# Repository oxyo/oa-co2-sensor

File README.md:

## Open Automation wireless CO2 sensor    

This device has been made on NXP LPC1114FN28 ARM MCU with winsensor CO2 sensor connected.
It uses [Ciseco XRF wireless RF radio UART serial data module][] to communicate with Open Automation Center

This simple device can measure CO2 concentration in air up to 2000 ppms. 
  
MBED firmware, schematics and board files provided. 
  
For more information please visit [openautomation.center](http://openautomation.center)

Licensed under [WTFPL license terms](http://www.wtfpl.net/)

[Ciseco XRF wireless RF radio UART serial data module]: http://shop.ciseco.co.uk/xrf-wireless-rf-radio-uart-serial-data-module-xbee-shaped/

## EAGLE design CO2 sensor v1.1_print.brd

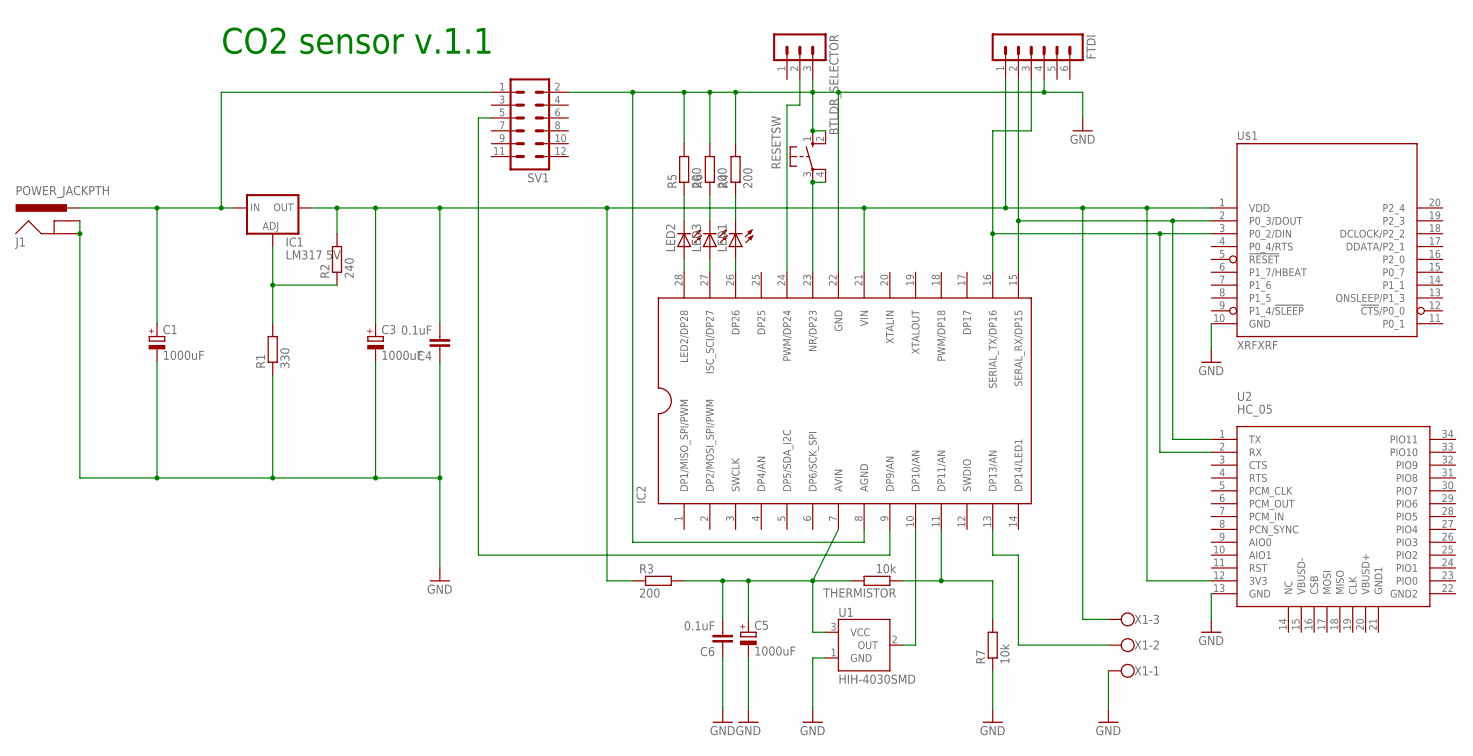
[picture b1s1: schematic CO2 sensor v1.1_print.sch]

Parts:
BTLDR_SELECTOR: MA03-1
C1, C3, C5: 1000uF; E5-10,5
C4, C6: 0.1uF; C050-025X075
FTDI: MA06-1
IC1: LM317 5V; 317TL
IC2: LPC1114FN28; DIP28
J1: POWER_JACKPTH; POWER_JACK_PTH
LED1, LED2, LED3: LED3MM
R1: 330; 0207/10
R2: 240; 0207/12
R3, R6: 200; 0207/12
R4: 200; 0207/10
R5: 200; 0207/2V
R7: 10k; 0207/12
RESETSW: 10-XX; B3F-10XX
SV1: MA06-2
THERMISTOR: 10k; 0207/5V
U1: HIH-4030SMD; HIH-4030
U2: HC_05; BLUETOOTH_SMD
U$1: XRFXRF; XRF
X1: W237-103

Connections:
GND: BTLDR_SELECTOR.3, C1.-, C3.-, C4.1, C5.-, C6.1, FTDI.4, IC2.8 (AGND), IC2.22 (GND), J1.GND, J1.GNDBREAK, R1.1, R4.2, R5.2, R6.2, R7.1, RESETSW.1 (S), RESETSW.2 (S1), SV1.2, U1.1 (GND), U2.13 (GND), U$1.10 (GND), X1.1
INPUT-CO2: IC2.9 (DP9/AN), SV1.5
INPUT-T: IC2.11 (DP11/AN), R7.2, THERMISTOR.1
INPUT-X: IC2.13 (DP13/AN), X1.2
LM317-5V: IC1.1 (ADJ), R1.2, R2.1
unnamed: LED1.K (C), R4.1
unnamed: IC2.28 (LED2/DP28), LED2.A
unnamed: C5.+, C6.2, IC2.7 (AVIN), R3.2, THERMISTOR.2, U1.3 (VCC)
unnamed: IC2.27 (ISC_SCI/DP27), LED3.A
unnamed: IC2.26 (DP26), LED1.A
unnamed: FTDI.2, IC2.15 (SERAL_RX/DP15), U2.1 (TX), U$1.2 (P0_3/DOUT)
unnamed: FTDI.3, IC2.16 (SERIAL_TX/DP16), U2.2 (RX), U$1.3 (P0_2/DIN)
unnamed: IC2.10 (DP10/AN), U1.2 (OUT)
unnamed: LED3.K (C), R6.1
unnamed: LED2.K (C), R5.1
unnamed: IC2.23 (NR/DP23), RESETSW.3, RESETSW.4 (P1)
unnamed: BTLDR_SELECTOR.2, IC2.24 (PWM/DP24)
V3.3: C3.+, C4.2, FTDI.1, IC1.2 (OUT), IC2.21 (VIN), R2.2, R3.1, U2.12 (3V3), U$1.1 (VDD), X1.3
V5: C1.+, IC1.3 (IN), J1.PWR, SV1.1

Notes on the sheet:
CO2 sensor v.1.1

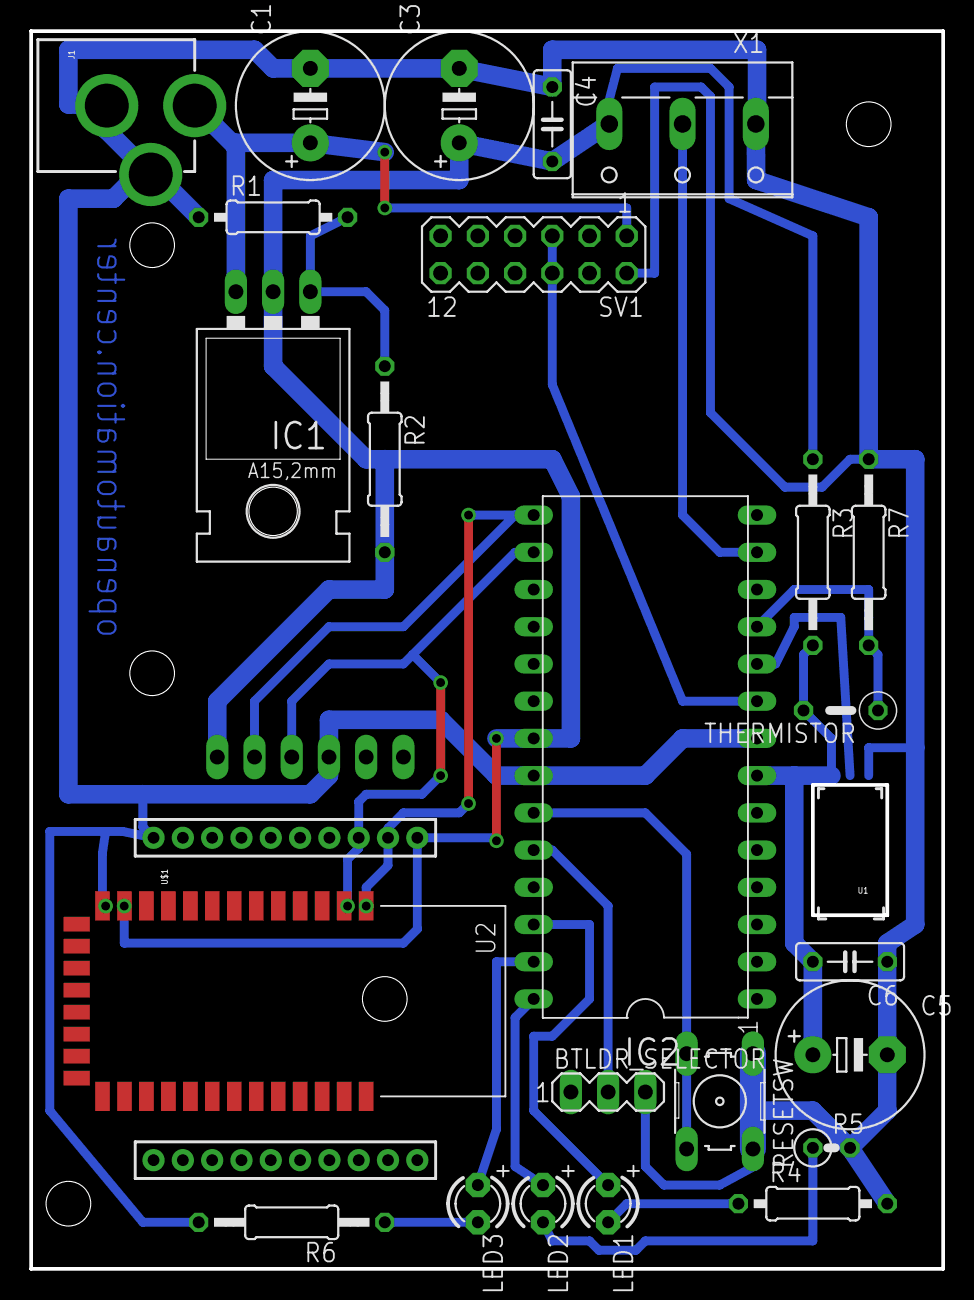
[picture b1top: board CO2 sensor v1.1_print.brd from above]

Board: 2 copper layers, 62.2 x 84.5 mm, 27 parts (1 on the bottom side), 19 nets.

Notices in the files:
parts and their libraries:
SparkFun-Connectors: Licensing: CC v3.0 Share-Alike You are welcome to use this library for commercial purposes.
